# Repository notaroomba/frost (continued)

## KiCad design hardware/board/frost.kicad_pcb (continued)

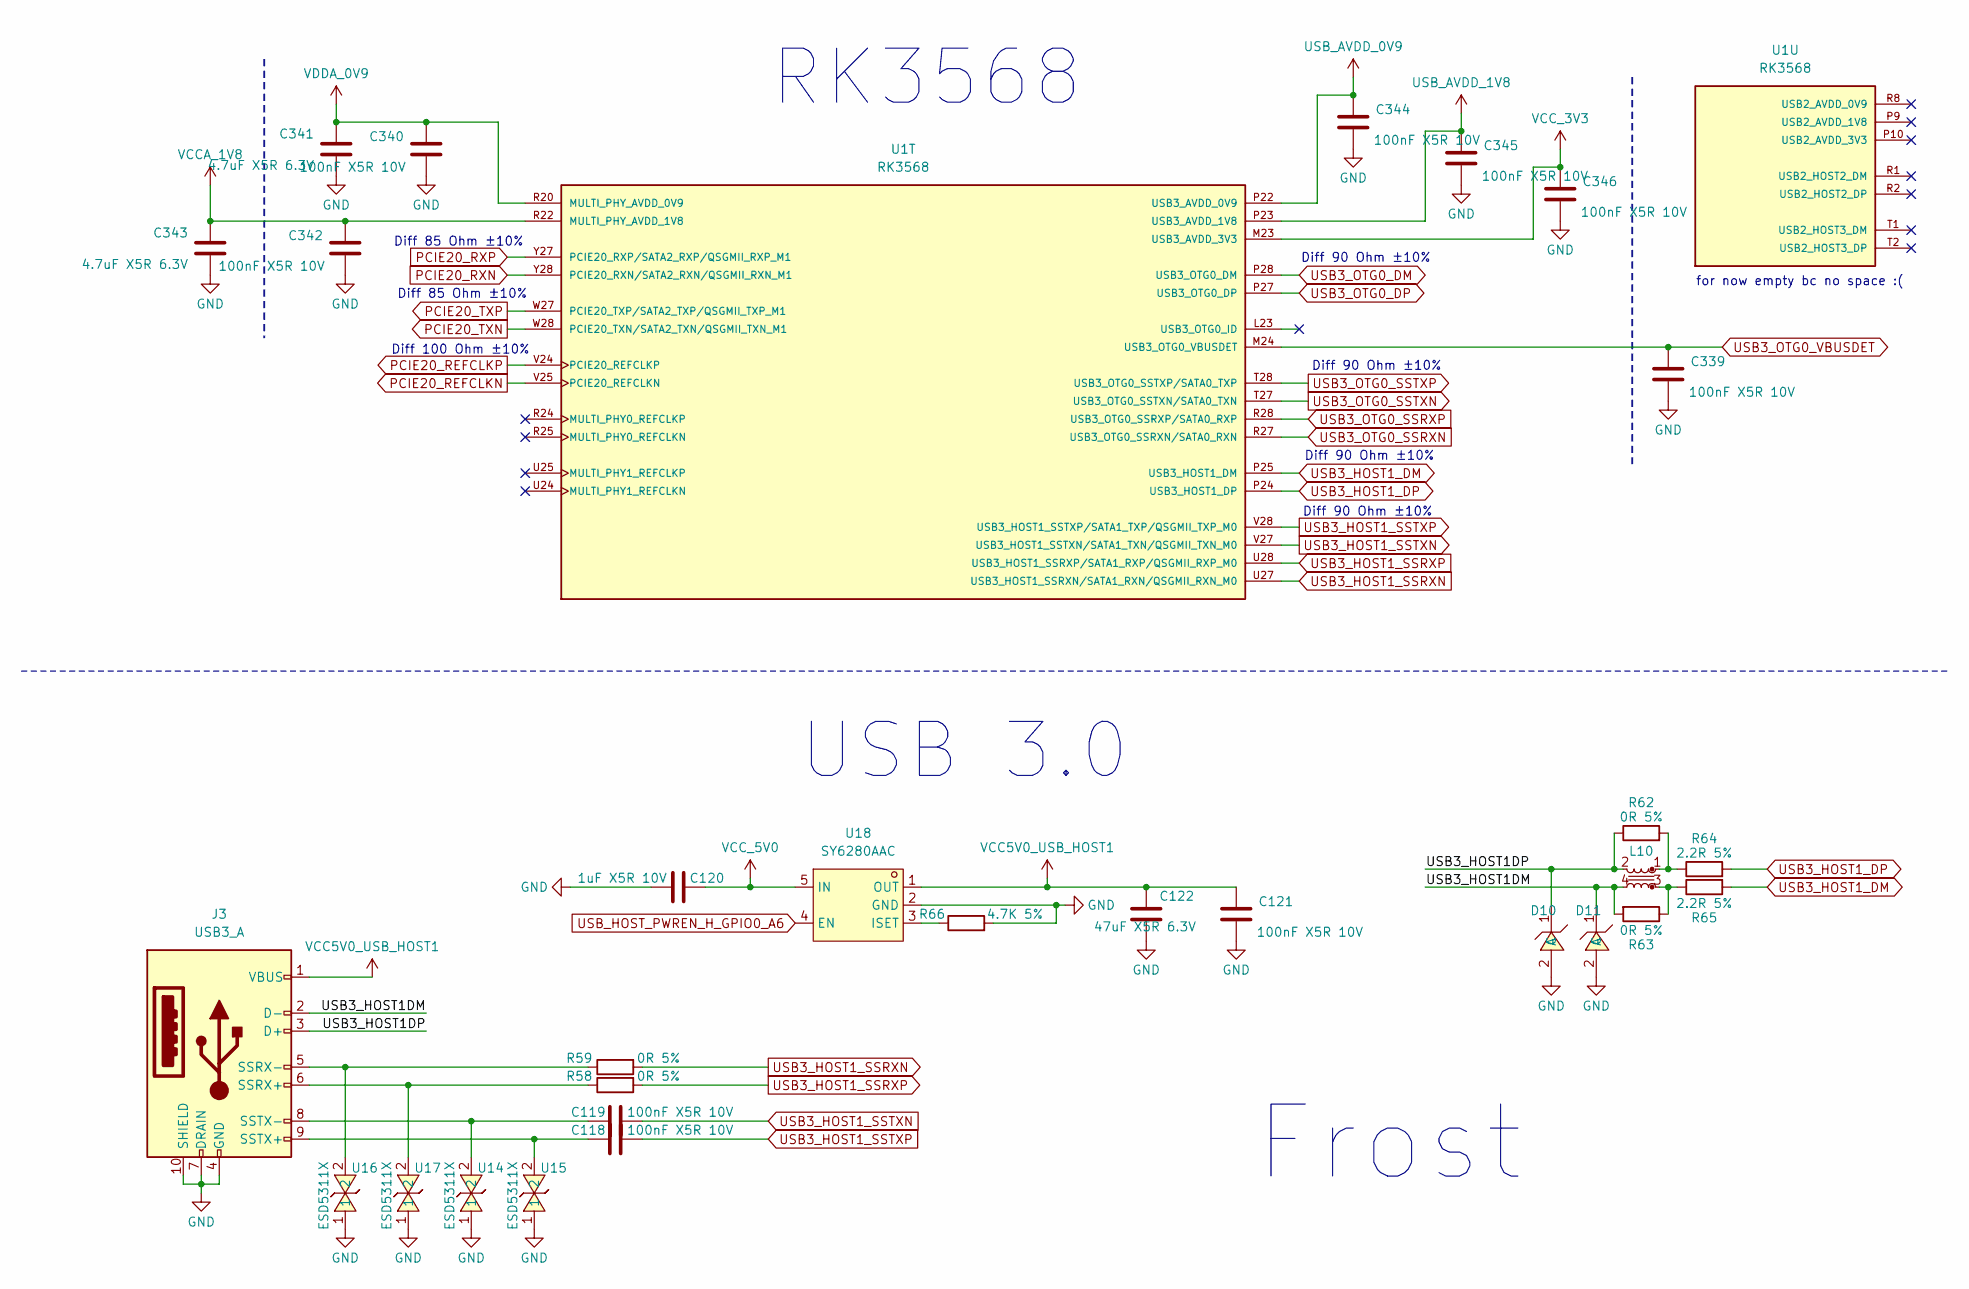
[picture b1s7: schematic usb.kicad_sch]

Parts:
C118, C119, C340, C342, C344, C345, C346: 100nF X5R 10V; C_0201_0603Metric
C120: 1uF X5R 10V; C_0402_1005Metric
C121, C339: 100nF X5R 10V; C_0402_1005Metric
C122: 47uF X5R 6.3V; C_0805_2012Metric
C341, C343: 4.7uF X5R 6.3V; C_0402_1005Metric
D10, D11: BZT52C5V1_C173407; SOD-123_L2.7-W1.6-LS3.7-RD; LCSC Part C173407
J3: USB3_A; USB-A-SMD_U-A-39SS-W-1
L10: L_Iron_Coupled_Small; FILTER-SMD_4P-L2.0-W1.2-BL_DLW21H
R58, R59: 0R 5%; R_0201_0603Metric
R62, R63: 0R 5%; R_0402_1005Metric
R64, R65: 2.2R 5%; R_0402_1005Metric
R66: 4.7K 5%; R_0402_1005Metric
U1: RK3568; BGA636C65P28X28_1900X1900X168; PARTREV 1.3; LCSC C3345225
U14, U15, U16, U17: ESD5311X; DFN1006-2L-BI; LCSC Part C2844730
U18: SY6280AAC; SOT-23-5_L3.0-W1.7-P0.95-LS2.8-BL; LCSC Part C55136

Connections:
/USB/USB3_HOST1DM: D11.1 (C), J3.2 (D-), L10.4, R63.2
/USB/USB3_HOST1DP: D10.1 (C), J3.3 (D+), L10.2, R62.1
unnamed: J3.6 (SSRX+), R58.1, U17.2
unnamed: J3.5 (SSRX-), R59.1, U16.2
unnamed: C118.1, J3.9 (SSTX+), U15.2
unnamed: C119.1, J3.8 (SSTX-), U14.2
unnamed: L10.1, R62.2, R64.1
unnamed: L10.3, R63.1, R65.1
unnamed: R66.1, U18.3 (ISET)
PCIE20_REFCLKN: U1.V25 (PCIE20_REFCLKN); also elsewhere on the board
PCIE20_REFCLKP: U1.V24 (PCIE20_REFCLKP); also elsewhere on the board
PCIE20_RXN: U1.Y28 (PCIE20_RXN/SATA2_RXN/QSGMII_RXN_M1); also elsewhere on the board
PCIE20_RXP: U1.Y27 (PCIE20_RXP/SATA2_RXP/QSGMII_RXP_M1); also elsewhere on the board
PCIE20_TXN: U1.W28 (PCIE20_TXN/SATA2_TXN/QSGMII_TXN_M1); also elsewhere on the board
PCIE20_TXP: U1.W27 (PCIE20_TXP/SATA2_TXP/QSGMII_TXP_M1); also elsewhere on the board
USB3_HOST1_DM: R65.2, U1.P25 (USB3_HOST1_DM)
USB3_HOST1_DP: R64.2, U1.P24 (USB3_HOST1_DP)
USB3_HOST1_SSRXN: R59.2, U1.U27 (USB3_HOST1_SSRXN/SATA1_RXN/QSGMII_RXN_M0)
USB3_HOST1_SSRXP: R58.2, U1.U28 (USB3_HOST1_SSRXP/SATA1_RXP/QSGMII_RXP_M0)
USB3_HOST1_SSTXN: C119.2, U1.V27 (USB3_HOST1_SSTXN/SATA1_TXN/QSGMII_TXN_M0)
USB3_HOST1_SSTXP: C118.2, U1.V28 (USB3_HOST1_SSTXP/SATA1_TXP/QSGMII_TXP_M0)
USB3_OTG0_DM: U1.P28 (USB3_OTG0_DM); also elsewhere on the board
USB3_OTG0_DP: U1.P27 (USB3_OTG0_DP); also elsewhere on the board
USB3_OTG0_SSRXN: U1.R27 (USB3_OTG0_SSRXN/SATA0_RXN); also elsewhere on the board
USB3_OTG0_SSRXP: U1.R28 (USB3_OTG0_SSRXP/SATA0_RXP); also elsewhere on the board
USB3_OTG0_SSTXN: U1.T27 (USB3_OTG0_SSTXN/SATA0_TXN); also elsewhere on the board
USB3_OTG0_SSTXP: U1.T28 (USB3_OTG0_SSTXP/SATA0_TXP); also elsewhere on the board
USB3_OTG0_VBUSDET: C339.1, U1.M24 (USB3_OTG0_VBUSDET); also elsewhere on the board
USB_AVDD_0V9: C344.1, U1.P22 (USB3_AVDD_0V9); also elsewhere on the board
USB_AVDD_1V8: C345.1, U1.P23 (USB3_AVDD_1V8); also elsewhere on the board
USB_HOST_PWREN_H_GPIO0_A6: U18.4 (EN); also elsewhere on the board
VCC5V0_USB_HOST1: C121.1, C122.2, J3.1 (VBUS), U18.1 (OUT)
VCCA_1V8: C342.1, C343.1, U1.R22 (MULTI_PHY_AVDD_1V8); also elsewhere on the board
VCC_3V3: C346.1, U1.M23 (USB3_AVDD_3V3); also elsewhere on the board
VCC_5V0: C120.2, U18.5 (IN); also elsewhere on the board
VDDA_0V9: C340.1, C341.1, U1.R20 (MULTI_PHY_AVDD_0V9), U1.R21 (MULTI_PHY_AVDD_0V9); also elsewhere on the board

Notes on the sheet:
Frost
Diff 85 Ohm ±10%
for now empty bc no space :(
Diff 90 Ohm ±10%
USB 3.0
Diff 100 Ohm ±10%
RK3568

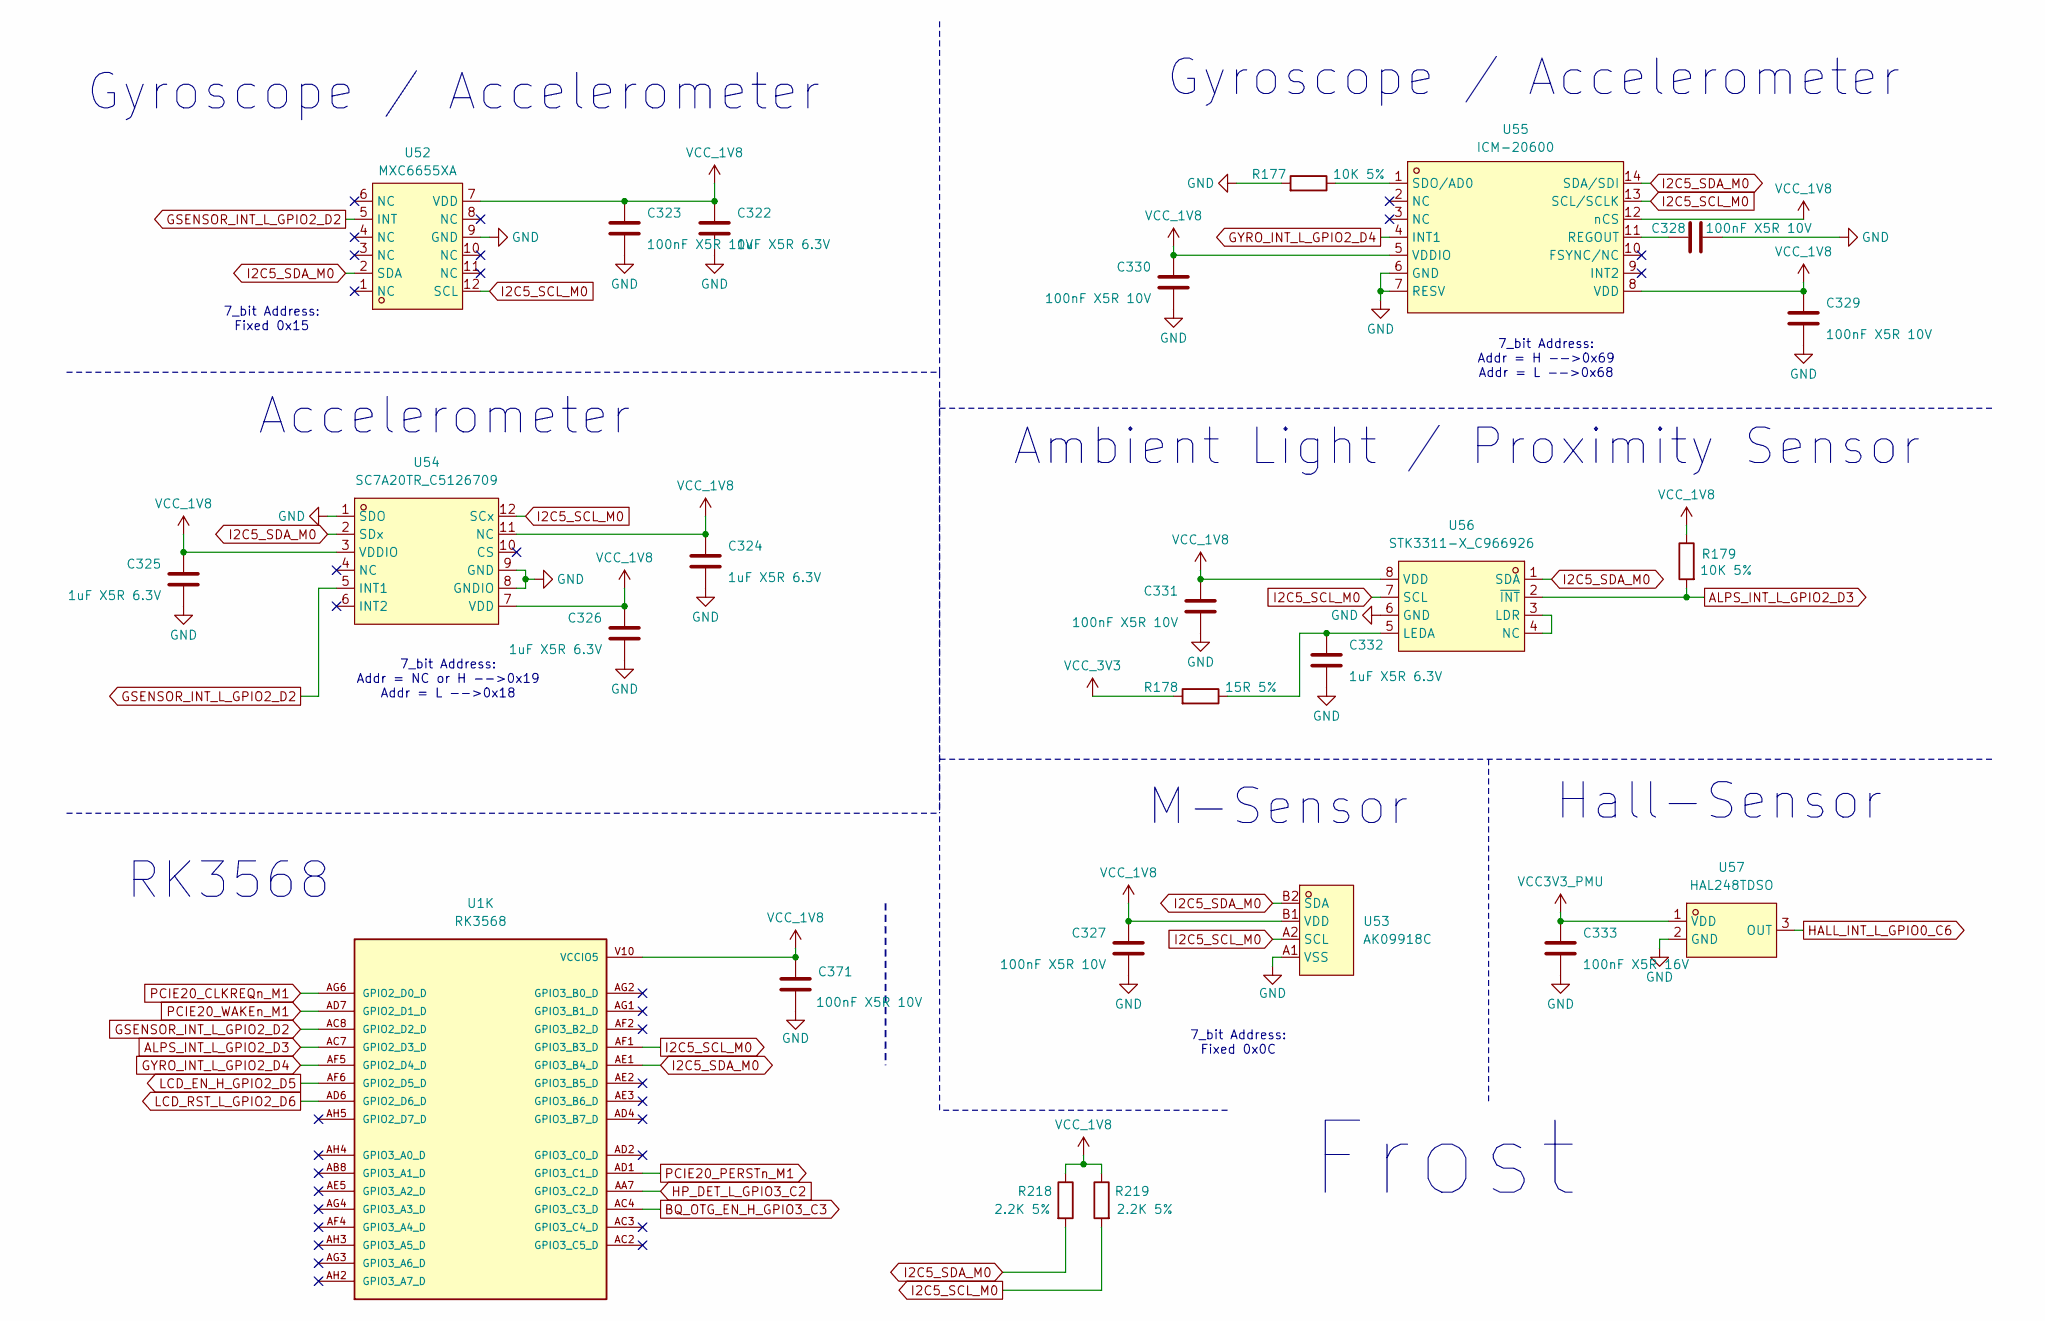
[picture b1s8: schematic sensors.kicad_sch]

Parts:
C322, C324, C325, C326, C332: 1uF X5R 6.3V; C_0402_1005Metric
C323, C327, C328, C329, C330, C331: 100nF X5R 10V; C_0402_1005Metric
C333: 100nF X5R 16V; C_0402_1005Metric
C371: 100nF X5R 10V; C_0201_0603Metric
R177, R179: 10K 5%; R_0402_1005Metric
R178: 15R 5%; R_0402_1005Metric
R218, R219: 2.2K 5%; R_0402_1005Metric
U1: RK3568; BGA636C65P28X28_1900X1900X168; PARTREV 1.3; LCSC C3345225
U52: MXC6655XA; LGA-12_L2.0-W2.0-P0.50-TL_BOSCH_BMA490L; LCSC Part C5189050
U53: AK09918C; WLCSP-4_L0.8-W0.8-R2-C2-P0.40-BL-1; LCSC Part C2655004
U54: SC7A20TR_C5126709; LGA-12_L2.0-W2.0-P0.50-BL; LCSC Part C5126709
U55: ICM-20600; LGA-14_L3.0-W2.5-P0.50-BL; LCSC Part C124140
U56: STK3311-X_C966926; LGA-8_L4.0-W2.4-P0.97-BR; LCSC Part C966926
U57: HAL248TDSO; SOT-23-3_L2.9-W1.6-P1.90-LS2.8-BR-CW; LCSC Part C19089538

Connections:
ALPS_INT_L_GPIO2_D3: R179.2, U1.AC7 (GPIO2_D3_D), U56.2 (~INT)
BQ_OTG_EN_H_GPIO3_C3: U1.AC4 (GPIO3_C3_D); also elsewhere on the board
GSENSOR_INT_L_GPIO2_D2: U1.AC8 (GPIO2_D2_D), U52.5 (INT), U54.5 (INT1)
GYRO_INT_L_GPIO2_D4: U1.AF5 (GPIO2_D4_D), U55.4 (INT1)
HALL_INT_L_GPIO0_C6: U57.3 (OUT); also elsewhere on the board
HP_DET_L_GPIO3_C2: U1.AA7 (GPIO3_C2_D); also elsewhere on the board
I2C5_SCL_M0: R219.2, U1.AF1 (GPIO3_B3_D), U52.12 (SCL), U53.A2 (SCL), U54.12 (SCx), U55.13 (SCL/SCLK), U56.7 (SCL)
I2C5_SDA_M0: R218.2, U1.AE1 (GPIO3_B4_D), U52.2 (SDA), U53.B2 (SDA), U54.2 (SDx), U55.14 (SDA/SDI), U56.1 (SDA)
LCD_EN_H_GPIO2_D5: U1.AF6 (GPIO2_D5_D)
LCD_RST_L_GPIO2_D6: U1.AD6 (GPIO2_D6_D); also elsewhere on the board
unnamed: C328.1, U55.11 (REGOUT)
unnamed: R177.1, U55.1 (SDO/AD0)
unnamed: U56.3 (LDR), U56.4 (NC)
unnamed: C332.1, R178.1, U56.5 (LEDA)
PCIE20_CLKREQn_M1: U1.AG6 (GPIO2_D0_D); also elsewhere on the board
PCIE20_PERSTn_M1: U1.AD1 (GPIO3_C1_D); also elsewhere on the board
PCIE20_WAKEn_M1: U1.AD7 (GPIO2_D1_D); also elsewhere on the board
VCC3V3_PMU: C333.1, U57.1 (VDD); also elsewhere on the board
VCC_1V8: C322.1, C323.1, C324.1, C325.1, C326.1, C327.1, C329.1, C330.1, C331.1, C371.1, R179.1, R218.1, R219.1, U1.V10 (VCCIO5), U1.V11 (VCCIO5), U52.7 (VDD), U53.B1 (VDD), U54.3 (VDDIO), U54.7 (VDD), U54.11 (NC), U55.5 (VDDIO), U55.8 (VDD), U55.12 (nCS), U56.8 (VDD); also elsewhere on the board
VCC_3V3: R178.2; also elsewhere on the board

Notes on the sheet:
RK3568
Frost
Gyroscope / Accelerometer
Ambient Light / Proximity Sensor
7_bit Address: Fixed 0x15
M-Sensor
Hall-Sensor
7_bit Address: Fixed 0x0C
7_bit Address: Addr = H -->0x69 Addr = L -->0x68
Accelerometer
7_bit Address: Addr = NC or H -->0x19 Addr = L -->0x18

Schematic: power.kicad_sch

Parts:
C3, C4, C5, C6, C21, C23: 10uF X5R 25V; C_0805_2012Metric
C7, C19, C30, C41, C43, C65, C69, C71, C76, C89, C112, C114, C334, C336: 10uF X5R 10V; C_0603_1608Metric
C8, C9, C10, C15, C20, C31, C32, C35, C40, C42, C53, C54, C61, C64, C68, C80, C97, C98, C113, C199, C335: 100nF X5R 10V; C_0402_1005Metric
C11, C12, C13, C14, C262, C265, C270, C372: 100nF X5R 10V; C_0201_0603Metric
C16, C17: 220pF C0G 25V; C_0402_1005Metric
C18, C50, C57, C74, C83, C84, C85: 1uF X5R 10V; C_0402_1005Metric
C22: 100pF C0G 50V; C_0402_1005Metric
C24: 4.7uF X5R 10V; C_0402_1005Metric
C25: 47nF X5R 25V; C_0402_1005Metric
C26, C27, C28, C29, C37: 10uF X5R 10V; C_0805_2012Metric
C33, C38: 22pF C0G 50V; C_0402_1005Metric
C34, C58, C59, C60, C62, C63, C66, C67, C70, C77, C78, C104, C105, C106, C255, C256, C257, C259, C260, C263, C269, C271, C272: 22uF X5R 6.3V; C_0603_1608Metric
C36, C55, C56: 100nF X5R 16V; C_0402_1005Metric
C39, C102, C103: 22uF X5R 10V; C_0805_2012Metric
C44, C86, C254, C261, C264: 4.7uF X5R 6.3V; C_0402_1005Metric
C45, C46, C47, C48, C49, C72, C73, C75, C79, C81, C82, C87, C88, C91, C93, C94, C101, C107, C108, C109, C110, C111, C115, C116, C266, C267: 1uF X5R 6.3V; C_0402_1005Metric
C51, C52: 20pF C0G 50V; C_0402_1005Metric
C90: 4.7uF X5R 10V; C_0603_1608Metric
C92: 2.2uF X5R 10V; C_0402_1005Metric
C95, C96: 27pF C0G 50V; C_0402_1005Metric
C99, C100: 680pF C0G 50V; C_0402_1005Metric
C117: 4.7uF X5R 6.3V; C_0603_1608Metric
C258, C268, C273: 10uF X5R 6.3V; C_0603_1608Metric
D1: BZT52C5V1_C173407; SOD-123_L2.7-W1.6-LS3.7-RD; LCSC Part C173407
D6, D7: ESD5344D; DFN2510-10_L2.5-W1.0-P0.50-BL; LCSC Part C6562203
D8: LED; LED_0603_1608Metric
D9: SS32; D_SMA
FB1, FB2, FB3, FB4, FB7, FB8, FB9, FB10: 120@100MHz 0.03R; L_0603_1608Metric; LCSC C85831
FB5, FB6: 180@100M 1.5A; L_0603_1608Metric; LCSC C268312
L1: L_Iron_Coupled_Small; FILTER-SMD_4P-L2.0-W1.2-BL_DLW21H
L2: SLO0520H1R0MTT; IND-SMD_L5.4-W5.1; LCSC Part C325980
L3, L4: LVF404026-2R2M-N; IND-SMD_L4.0-W4.0; LCSC Part C2847115
Q1: WPM3407-3/TR; SOT-23-3_L3.0-W1.7-P0.95-LS2.9-BR; LCSC Part C167139
Q2, Q5: SS8050; SOT-23
Q3, Q4, Q9: WPM2015-3/TR_C7472861; SOT-23-3_L2.9-W1.3-P1.90-LS2.4-BR; LCSC Part C7472861
R3: 0R; R_1206_3216Metric
R4: 470R 5%; R_0805_2012Metric
R5, R17, R20, R24, R26, R29, R34, R51, R53, R57, R190: 10K 5%; R_0402_1005Metric
R6: 15K 5%; R_0402_1005Metric
R7, R8: 2.2R 5%; R_0402_1005Metric
R9, R12, R19, R31, R32, R33, R45, R54, R55, R56: 0R 5%; R_0402_1005Metric
R10, R11: 0R 5%; R_0201_0603Metric
R13: 330R 5%; R_0402_1005Metric
R14, R40, R41, R42, R49: 100R 5%; R_0402_1005Metric
R15: 5.1K 1%; R_0402_1005Metric
R16, R37, R39: 30K 1%; R_0402_1005Metric
R18: 0.01R 1%; R_1206_3216Metric
R21: 232K 1%; R_0402_1005Metric
R22: 49.9K 1%; R_0402_1005Metric
R23, R30, R47, R50, R192: 100K 5%; R_0402_1005Metric
R25, R48, R52: 51K 5%; R_0402_1005Metric
R27: 360K 1%; R_0402_1005Metric
R28, R43: 47K 1%; R_0402_1005Metric
R35, R36, R220, R221, R223, R224: 22R 5%; R_0402_1005Metric
R38: 20K 1%; R_0402_1005Metric
R44: 120K 1%; R_0402_1005Metric
R46: 30K 5%; R_0402_1005Metric
R191: 100K 5%; R_0402_1005Metric; not fitted
U1: RK3568; BGA636C65P28X28_1900X1900X168; PARTREV 1.3; LCSC C3345225
U4: RK809-5; QFN-68_L7.0-W7.0-P0.35-BL-EP5.5; LCSC Part C2939628
U6: TMUXHS4212RKSR; TQFN-20_L4.5-W2.5-P0.50-BL-EP3.0; LCSC Part C2869871
U7: FUSB302BMPX; WQFN-14-1EP_2.5x2.5mm_P0.5mm_EP1.45x1.45mm
U8: BQ25890RTWR; WQFN-24_L4.0-W4.0-P0.50-BL-EP; LCSC Part C130451
U9: S2B-PH-K-S(LF)(SN); CONN-TH_S2B-PH-K-S-LF-SN; LCSC Part C173752
U10, U64, U65, U66, U67: FTC252012SR47MBCA; IND-SMD_L2.5-W2.0; LCSC Part C5832368
U11: RK860-0; WLCSP-20_L2.0-W1.6-R5-C4-P0.40-TL; LCSC Part C19188628
U12: SY7208ABC; SOT-23-6_L2.9-W1.6-P0.95-LS2.8-BR; LCSC Part C80514
U13: FTC252012SR24MBCA; IND-SMD_L2.5-W2.0_MHCHL2520; LCSC Part C5832366
U63: SY8089AAAC; SOT-23-5_L3.0-W1.7-P0.95-LS2.8-BR; LCSC Part C78988
U68, U69, U70, U71: ESD5341N; DFN1006-2L-RD; LCSC Part C3021106
USBC1: 105450-0101; USB-C-SMD_TYPE-C-USB-18; LCSC Part C134092
X2: Q13FC1350000400; FC-135R_L3.2-W1.5; LCSC Part C32346

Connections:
/Power/PMIC_XIN: C51.1, U4.50 (XIN), X2.2
/Power/PMIC_XOUT: C52.1, U4.51 (XOUT), X2.1
/Power/SNSN: C55.1, R19.2, U4.63 (SNSN)
/Power/SNSP: C55.2, R18.1, U4.62 (SNSP), U9.1
/Power/TYPEC_0_CC1: C16.1, U7.10 (CC1), U7.11 (CC1), U69.1, USBC1.A5 (CC1)
/Power/TYPEC_0_CC2: C17.1, U7.1 (CC2), U7.14 (CC2), U68.1, USBC1.B5 (CC2)
/Power/TYPEC_0_DM: L1.3, L1.4, R8.1, U71.1, USBC1.A7 (D-), USBC1.B6 (D+)
/Power/TYPEC_0_DP: L1.1, L1.2, R7.1, U70.1, USBC1.A6 (D+), USBC1.B7 (D-)
/Power/TYPEC_0_SSRX1N: D6.5, D6.6, U6.16 (B1n), USBC1.B10 (RX1-)
/Power/TYPEC_0_SSRX1P: D6.4, D6.7, U6.17 (B1p), USBC1.B11 (RX1+)
/Power/TYPEC_0_SSRX2N: D7.4, D7.7, U6.12 (C1n), USBC1.A10 (RX2-)
/Power/TYPEC_0_SSRX2P: D7.5, D7.6, U6.13 (C1p), USBC1.A11 (RX2+)
/Power/TYPEC_0_SSTX1N: C13.1, D6.2, D6.9, USBC1.A3 (TX1-)
/Power/TYPEC_0_SSTX1P: C14.1, D6.1, D6.10, USBC1.A2 (TX1+)
/Power/TYPEC_0_SSTX2N: C11.1, D7.1, D7.10, USBC1.B3 (TX2-)
/Power/TYPEC_0_SSTX2P: C12.1, D7.2, D7.9, USBC1.B2 (TX2+)
BQ_OTG_EN_H_GPIO3_C3: U8.8 (OTG); also elsewhere on the board
CHG_INT_L_GPIO0_C2: U8.7 (INT); also elsewhere on the board
CHG_REF: C24.1, D8.2 (A), R15.1, U8.22 (REGN)
FLASH_VOL_SEL: R57.1; also elsewhere on the board
HPL_OUT: U4.39 (HPL_OUT); also elsewhere on the board
HPR_OUT: U4.41 (HPR_OUT); also elsewhere on the board
HP_SNS: U4.40 (HP_SNS); also elsewhere on the board
I2C0_SCL_PMIC: R35.2, U7.6 (SCL), U8.5 (SCL), U11.A3 (SCL); also elsewhere on the board
I2C0_SDA_PMIC: R36.2, U7.7 (SDA), U8.6 (SDA), U11.B1 (SDA); also elsewhere on the board
I2S1_LRCK_TX_M0_PMIC: R223.2, U4.14 (LRCLK)
I2S1_MCLK_M0_PMIC: R220.2, U4.16 (MCLK)
I2S1_SCLK_TX_M0_PMIC: R221.2, U4.15 (BCLK)
I2S1_SDI0_M0/PDM_SDI0_M0_PMIC: U1.B21 (GPIO1_B3_D), U4.18 (SDO/PDMDATA)
I2S1_SDO0_M0_PMIC: U1.B20 (GPIO1_A7_D), U4.17 (SDI)
LCD0_PWREN_H_GPIO0_C7: R53.2; also elsewhere on the board
MIC1_INN: C97.1; also elsewhere on the board
MIC1_INP: C98.1
MIPI_AVDD_0V9: FB9.2; also elsewhere on the board
MIPI_AVDD_1V8: FB10.2; also elsewhere on the board
unnamed: C25.1, L2.2, U8.19 (SW), U8.20 (SW)
unnamed: D8.1 (K), R13.2
unnamed: D9.2 (A), L3.2, U12.1 (LX)
unnamed: C37.1, L3.1, Q1.3 (D), U12.4 (EN), U12.5 (IN)
unnamed: Q1.1 (G), R24.2
unnamed: Q2.1 (B), R25.2, R26.2
unnamed: Q2.3 (C), R24.1
unnamed: C42.2, Q3.1 (G), R29.2
unnamed: C113.2, Q4.1 (G), R50.1, R51.2
unnamed: Q5.1 (B), R52.2, R53.1
unnamed: Q5.3 (C), R51.1
unnamed: C335.2, Q9.1 (G), R190.2, R192.1
unnamed: R37.1, R39.2
unnamed: R220.1, U1.A19 (GPIO1_A2_D)
unnamed: R221.1, U1.B19 (GPIO1_A3_D)
unnamed: R223.1, U1.A20 (GPIO1_A5_D)
unnamed: R224.1, U1.C20 (GPIO1_A6_D)
unnamed: R37.2, R38.2, U4.56 (BATDIV)
unnamed: R33.2, U4.68 (CLK32K)
unnamed: C90.2, U4.36 (CPN)
unnamed: C90.1, U4.37 (CPP)
unnamed: R43.1, R44.2, U4.27 (FB3)
unnamed: R45.1, U4.59 (FB5)
unnamed: C96.1, C97.2, U4.42 (MICIN)
unnamed: C95.1, C98.2, U4.43 (MICIP)
unnamed: R35.1, U4.1 (SCL)
unnamed: R36.1, U4.2 (SDA)
unnamed: FB6.2, U4.34 (SPKN_OUT)
unnamed: FB5.2, U4.32 (SPKP_OUT)
unnamed: U4.12 (SW1), U64.2
unnamed: U4.9 (SW2), U10.2
unnamed: U4.25 (SW3), U65.2
unnamed: U4.65 (SW4), U67.1
unnamed: U4.53 (SW5), U66.1
unnamed: C94.1, U4.44 (VCC_1P8A)
unnamed: C93.1, U4.48 (VCC_1P8D)
unnamed: C91.1, U4.38 (VCC_CPVDD)
unnamed: C92.1, U4.35 (VCC_CPVSS)
unnamed: C89.1, FB4.2, U4.33 (VCC_SPK_HP)
unnamed: C80.2, R46.1, R47.1, U4.61 (VDC)
unnamed: C50.1, U4.46 (VREF)
unnamed: R10.2, U6.8 (A1n)
unnamed: R11.2, U6.7 (A1p)
unnamed: C13.2, U6.18 (B0n)
unnamed: C14.2, U6.19 (B0p)
unnamed: C11.2, U6.14 (C0n)
unnamed: C12.2, U6.15 (C0p)
unnamed: R9.2, U6.2 (OEn)
unnamed: C25.2, U8.21 (BTST)
unnamed: R14.1, U8.10 (ILIM)
unnamed: C23.2, U8.23 (PMID)
unnamed: R13.1, U8.4 (STAT)
unnamed: C22.1, R15.2, R16.1, R17.1, U8.11 (TS)
unnamed: R12.1, U8.9 (~CE)
unnamed: R48.1, U11.A2 (EN)
unnamed: U11.D3 (LX), U11.D4 (LX), U11.E3 (LX), U11.E4 (LX), U13.1
unnamed: C38.2, R27.1, R28.2, U12.3 (FB)
unnamed: C32.1, R20.1, U63.1 (EN)
unnamed: C33.2, R21.1, R22.2, U63.5 (FB)
unnamed: L4.1, U63.3 (LX)
PDM_CLK0_M0_PMIC: R224.2, U4.19 (PDMCLK)
PMIC_32KOUT_WIFI: R33.1; also elsewhere on the board
PMIC_INT_L: U4.7 (INT); also elsewhere on the board
PMIC_PWRON: C54.1, U4.52 (PWRON); also elsewhere on the board
PMIC_SLEEP_H: R29.1, R30.2, U4.49 (SLEEP), U11.A1 (VSEL); also elsewhere on the board
PMUIO2: C115.1, R54.1, R55.2; also elsewhere on the board
RESETn: C53.1, R34.2, U4.67 (RESETB); also elsewhere on the board
SDMMC0_PWREN_L: R190.1, R191.2; also elsewhere on the board
SPKN_OUT: C100.2, FB6.1
SPKP_OUT: C99.2, FB5.1
TYPEC_SW_SEL_GPIO4_D2: U6.9 (SEL); also elsewhere on the board
USB3_OTG0_DM: R8.2; also elsewhere on the board
USB3_OTG0_DP: R7.2; also elsewhere on the board
USB3_OTG0_SSRXN: R10.1; also elsewhere on the board
USB3_OTG0_SSRXP: R11.1; also elsewhere on the board
USB3_OTG0_SSTXN: U6.4 (A0n); also elsewhere on the board
USB3_OTG0_SSTXP: U6.3 (A0p); also elsewhere on the board
USB3_OTG0_VBUSDET: R5.2, R6.2; also elsewhere on the board
USB5V0_EN_H_GPIO0_D6: R26.1; also elsewhere on the board
USBCC_INT_L_GPIO0_C5: U7.5 (INT_N); also elsewhere on the board
USB_AVDD_0V9: FB7.2; also elsewhere on the board
USB_AVDD_1V8: FB8.2; also elsewhere on the board
VBUS_DC5V: D1.1 (C), R4.2, R5.1, R47.2
VBUS_TYPEC: C5.1, C6.1, C15.1, R3.2, R4.1, U7.2 (VBUS)
VBUS_TYPEC_0: C3.1, C4.1, C21.1, R3.1, U8.1 (VBUS), USBC1.A4 (VBUS), USBC1.A9 (VBUS), USBC1.B4 (VBUS), USBC1.B9 (VBUS)
VCC3V3_LCD0: C114.1, Q4.3 (D); also elsewhere on the board
VCC3V3_PMU: C18.1, C88.1, R20.2, R34.1, R48.2, R57.2, U4.31 (LDO6), U7.3 (VDD), U7.4 (VDD); also elsewhere on the board
VCC3V3_SD: C79.2, C336.1, Q9.3 (D), U4.58 (SWOUT2); also elsewhere on the board
VCC3V3_SYS: C19.1, C20.1, C33.1, C34.1, C35.1, C41.1, C42.1, C75.2, C112.1, C113.1, C334.1, C335.1, L4.2, Q3.2 (S), Q4.2 (S), Q9.2 (S), R21.2, R50.2, R192.2, U4.57 (VCC8), U7.12 (VCONN), U7.13 (VCONN); also elsewhere on the board
VCC3V3_U3_SW: C7.1, C8.1, C9.1, C10.1, FB1.2, U6.1 (RSVD1), U6.6 (VCC), U6.10 (RSVD2)
VCCA1V8_IMAGE: C48.1, C111.1, FB3.2, FB10.1; also elsewhere on the board
VCCA1V8_IMAGE_P: C81.2, U4.6 (LDO9); also elsewhere on the board
VCCA1V8_PMU: C82.2, R54.2, U4.5 (LDO8); also elsewhere on the board
VCCA_1V8: C49.1, C109.1, FB8.1, R32.1; also elsewhere on the board
VCCA_1V8_P: C101.2, R32.2, U4.3 (LDO7)
VCCIO_ACODEC: C86.2, C372.1, U1.H17 (VCCIO1), U4.28 (LDO4); also elsewhere on the board
VCCIO_FLASH: C117.1, R56.1; also elsewhere on the board
VCCIO_SD: C87.1, U4.29 (LDO5); also elsewhere on the board
VCCIO_WL: C116.1, R55.1; also elsewhere on the board
VCC_1V8: C47.1, C77.1, C78.1, FB3.1, R45.2, R56.2, U66.2; also elsewhere on the board
VCC_3V3: C43.1, FB1.1, Q3.3 (D); also elsewhere on the board
VCC_5V0: C38.1, C39.1, C40.1, D9.1 (K), FB4.1, R27.2; also elsewhere on the board
VCC_BAT: C28.1, C29.1, C56.1, R39.1, U8.13 (BAT), U8.14 (BAT), U9.2
VCC_DDR: C70.1, C71.1, R43.2, U4.26 (VBUCK3), U65.1; also elsewhere on the board
VCC_SYSIN: C26.1, C27.1, C30.1, C31.1, C36.1, C57.1, C58.1, C65.1, C69.1, C72.2, C73.2, C74.2, C76.1, C102.1, C103.1, L2.1, Q1.2 (S), R23.2, U4.4 (VCC7), U4.10 (VCC2), U4.11 (VCC1), U4.22 (VCC5), U4.24 (VCC3), U4.30 (VCC6), U4.45 (VCC_RTC), U4.54 (VCC9), U4.66 (VCC4), U8.15 (SYS), U8.16 (SYS), U11.D1 (VIN), U11.D2 (VIN), U11.E1 (VIN), U11.E2 (VIN), U63.4 (IN); also elsewhere on the board
VDDA0V9_IMAGE: C45.1, C110.1, FB2.2, FB9.1; also elsewhere on the board
VDDA0V9_IMAGE_P: C83.2, U4.23 (LDO1); also elsewhere on the board
VDDA0V9_PMU: C85.2, U4.20 (LDO3); also elsewhere on the board
VDDA_0V9: C46.1, C108.1, FB7.1, R31.1; also elsewhere on the board
VDDA_0V9_P: C84.2, R31.2, U4.21 (LDO2)
VDD_CPU: C104.1, C105.1, C106.1, C107.2, C199.1, C254.1, C255.1, C256.1, C257.1, R49.1, U1.J15 (VDD_CPU), U1.K15 (VDD_CPU), U1.K16 (VDD_CPU), U1.K17 (VDD_CPU), U1.K18 (VDD_CPU), U1.L15 (VDD_CPU), U1.L16 (VDD_CPU), U1.L17 (VDD_CPU), U1.L18 (VDD_CPU), U1.M17 (VDD_CPU), U13.2
VDD_CPU_COM: C107.1, R49.2, U1.M15 (VDD_CPU_COM), U11.A4 (VOUT)
VDD_GPU: C62.1, C63.1, C64.1, C64.2, C258.1, C259.1, C260.1, C261.1, C262.1, R41.1, R41.2, U1.R13 (VDD_GPU), U1.T13 (VDD_GPU), U1.U11 (VDD_GPU), U1.U12 (VDD_GPU), U1.U13 (VDD_GPU), U4.8 (FB2), U10.1
VDD_LOGIC: C44.1, C59.1, C60.1, C61.1, C61.2, C263.1, C264.1, C265.1, C266.1, C267.1, C268.1, C269.1, FB2.1, R40.1, R40.2, U1.L12 (VDD_LOGIC), U1.M12 (VDD_LOGIC), U1.N13 (VDD_LOGIC), U1.N16 (VDD_LOGIC), U1.P13 (VDD_LOGIC), U1.P16 (VDD_LOGIC), U1.R12 (VDD_LOGIC), U1.R16 (VDD_LOGIC), U1.T12 (VDD_LOGIC), U1.T16 (VDD_LOGIC), U4.13 (FB1), U64.1
VDD_NPU: C66.1, C67.1, C68.1, C68.2, C270.1, C271.1, C272.1, C273.1, R42.1, R42.2, U1.M19 (VDD_NPU), U1.N19 (VDD_NPU), U1.P18 (VDD_NPU), U1.P19 (VDD_NPU), U1.P20 (VDD_NPU), U4.64 (FB4), U67.2

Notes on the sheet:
LCD Power
Should be placed under
VCC_3V3_SD
USB/MIPI PHY Power
USB-C / ESD
VDD_CPU
I2C if needed
USB-C PD
Power Schematics
VCC/VDDA
Differential Channel Crossbar Switch
VCC_3V3 (OFF under SLEEP)
Should be placed close
Peripheral power input source
Check feedback resistor depending on RAM type 47k is for LPDDR4
Power
Frost
FLASH
WIFI/BT IO and CTL IO Power
VCC_5V0
Close to BAT SNSP/N are differential
Note: FLASH_VOL_SEL is pulled up if 1.8v and down if 3.3v
VCC3V3_SYS
PMIC RK809
RK3568
Charger IC

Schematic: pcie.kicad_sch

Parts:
C297, C298, C299, C300: 220nF X5R 10V; C_0201_0603Metric
C301, C303: 22uF X5R 6.3V; C_0603_1608Metric
C302, C304, C308, C310, C313, C316, C317, C321: 100nF X5R 10V; C_0402_1005Metric
C305, C306: 18pF C0G 50V; C_0402_1005Metric
C307, C309, C312: 1uF X5R 10V; C_0402_1005Metric
C311, C314: 4.7F X5R 6.3V; C_0402_1005Metric
C315: 10uF X5R 10V; C_0603_1608Metric
C318: 22pF C0G 50V; C_0402_1005Metric
C319: 10uF X5R 6.3V; C_0603_1608Metric
C320: 22pF C0G 50V; CP_Elec_6.3x5.9; LCSC Part C186713
C347, C350: 4.7uF X5R 6.3V; C_0402_1005Metric
C348, C349: 100nF X5R 10V; C_0201_0603Metric
CN2: 1-2199230-5; PCIE-SMD_75P-P0.50_1-2199230-5; LCSC Part C590854
L11: LVF404026-2R2M-N; IND-SMD_L4.0-W4.0; LCSC Part C2847115
R152, R153, R154, R155: 22R 5%; R_0402_1005Metric
R156: 2.2R 5%; R_0402_1005Metric
R157, R158, R161, R162: 33R 5%; R_0201_0603Metric
R159, R160, R163, R164: 49.9R 1%; R_0201_0603Metric
R165, R173: 470R 1%; R_0402_1005Metric
R166, R167, R169, R171, R172, R174: 10K 5%; R_0402_1005Metric
R168, R170: 10K 5%; R_0402_1005Metric; not fitted
R175: 232K 1%; R_0402_1005Metric
R176: 49.9K 1%; R_0402_1005Metric
R197: 200R 1%; R_0201_0603Metric
TP1, TP2, TP3, TP4: TestPoint; TestPoint_Pad_D1.0mm
U1: RK3568; BGA636C65P28X28_1900X1900X168; PARTREV 1.3; LCSC C3345225
U46: PI6C557-03BLE; TSSOP-16_L5.0-W4.4-P0.65-LS6.4-BL; LCSC Part C150743
U50: TP5108E23E-33; SOT-23-5_L3.0-W1.7-P0.95-LS2.8-BL; LCSC Part C587168
U51: SY8089AAAC; SOT-23-5_L3.0-W1.7-P0.95-LS2.8-BR; LCSC Part C78988
X6: X322525MOB4SI; CRYSTAL-SMD_4P-L3.2-W2.5-BL; LCSC Part C9006

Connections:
/PCIE/PI6C_03_OE: R172.1, U46.6 (OE)
/PCIE/PI6C_03_S0: R166.1, U46.1 (S0)
/PCIE/PI6C_03_S1: R167.1, U46.2 (S1)
/PCIE/PI6C_03_SS0: R168.1, R169.1, U46.3 (SS0)
/PCIE/PI6C_03_SS1: R170.1, R171.1, U46.8 (SS1)
unnamed: C297.1, CN2.49
unnamed: C298.1, CN2.47
unnamed: C299.1, CN2.35
unnamed: C300.1, CN2.37
unnamed: CN2.10, TP4.1
unnamed: CN2.38, TP1.1
unnamed: CN2.50, R153.2
unnamed: CN2.52, R152.2
unnamed: CN2.54, R154.2
unnamed: CN2.56, TP3.1
unnamed: CN2.58, TP2.1
unnamed: R197.2, U1.U19 (PCIE30_RESREF)
unnamed: R158.2, U46.15 (CLK0)
unnamed: R161.2, U46.11 (CLK1)
unnamed: R165.1, U46.9 (IREF)
unnamed: C309.1, C310.1, R156.2, U46.12 (VDDA)
unnamed: C306.1, U46.4 (X1/CLK), X6.3 (OSC2)
unnamed: R155.1, U46.5 (X2)
unnamed: R157.2, U46.14 (~CLK0)
unnamed: R162.2, U46.10 (~CLK1)
unnamed: C313.1, R173.1, U50.3 (CE)
unnamed: C317.1, R174.2, U51.1 (EN)
unnamed: C318.2, R175.2, R176.1, U51.5 (FB)
unnamed: L11.1, U51.3 (LX)
unnamed: C305.1, R155.2, X6.1 (OSC1)
PCIE30X2_CLKREQn_M2: R152.1; also elsewhere on the board
PCIE30X2_PERSTn_M2: R153.1; also elsewhere on the board
PCIE30X2_WAKEn_M2: R154.1; also elsewhere on the board
PCIE30_REFCLKN_CON: CN2.53, R157.1, R159.1
PCIE30_REFCLKN_IN: R162.1, R163.1, U1.AA25 (PCIE30_REFCLKN_IN)
PCIE30_REFCLKP_CON: CN2.55, R158.1, R160.1
PCIE30_REFCLKP_IN: R161.1, R164.1, U1.Y25 (PCIE30_REFCLKP_IN)
PCIE30_RX0N: CN2.41, U1.AC27 (PCIE30_RX0N)
PCIE30_RX0P: CN2.43, U1.AC28 (PCIE30_RX0P)
PCIE30_RX1N: CN2.29, U1.AD27 (PCIE30_RX1N)
PCIE30_RX1P: CN2.31, U1.AD28 (PCIE30_RX1P)
PCIE30_TX0N: C298.2, U1.AA27 (PCIE30_TX0N)
PCIE30_TX0P: C297.2, U1.AA28 (PCIE30_TX0P)
PCIE30_TX1N: C299.2, U1.AB27 (PCIE30_TX1N)
PCIE30_TX1P: C300.2, U1.AB28 (PCIE30_TX1P)
PCIE_PWREN_H_GPIO0_D4: R173.2, R174.1; also elsewhere on the board
VCC3V3_PCIE30: C301.1, C302.1, C303.1, C304.1, C318.1, C319.1, C320.1, C321.1, CN2.2, CN2.4, CN2.70, CN2.72, CN2.74, L11.2, R175.1
VCC3V3_PI6C_03: C307.1, C308.1, C311.1, C314.1, R156.1, R166.2, R168.2, R170.2, R172.2, U46.16 (VDDX), U50.5 (OUT)
VCCA_1V8: C349.1, C350.1, U1.U22 (PCIE30_AVDD_1V8); also elsewhere on the board
VCC_SYSIN: C312.1, C315.1, C316.1, U50.1 (VIN), U51.4 (IN); also elsewhere on the board
VDDA_0V9: C347.1, C348.1, U1.U20 (PCIE30_AVDD_0V9), U1.U21 (PCIE30_AVDD_0V9); also elsewhere on the board

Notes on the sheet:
Diff 100 Ohm ±10%
M.2 Type B
Diff 85 Ohm ±10%
RK3568
Clock Generator
Frost
Power / Decoupling

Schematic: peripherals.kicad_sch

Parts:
C1, C2: 10pF C0G 50V; C_0402_1005Metric
C198, C253: 100nF X5R 10V; C_0402_1005Metric
C252: 220pF C0G 25V; C_0402_1005Metric
C284, C286, C288, C289, C292, C293, C294, C295, C358, C359: 100nF X5R 10V; C_0201_0603Metric
C285, C287, C290, C291, C296: 1uF X5R 10V; C_0402_1005Metric
C353, C354, C355, C356, C357: 1nF X5R 10V; C_0402_1005Metric
CN1: PJ-393 8PJ; AUDIO-SMD_PJ-393-8PJ; LCSC Part C668609
J4: Conn_01x04; PinHeader_1x04_P2.54mm_Vertical
R1: 22R 5%; R_0402_1005Metric
R2: 1M 5%; R_0402_1005Metric
R129: 1K 5%; R_0402_1005Metric
R139, R148, R149: 100K 5%; R_0402_1005Metric
R140, R141, R145, R151: 0R 5%; R_0402_1005Metric
R146, R193, R194: 2.2K 5%; R_0402_1005Metric
R147, R180, R181, R183, R184, R185: 100R 5%; R_0402_1005Metric
R182: 120R 5%; R_0402_1005Metric
R186, R188: 10K 1%; R_0402_1005Metric
R187, R189: 10K 1%; R_0402_1005Metric; not fitted
R198, R199: 10K 5%; R_0402_1005Metric
SW1, SW2, SW3: TS24CA; SW-SMD_2P-TS24CA; LCSC Part C393942
TP10, TP11: TestPoint; TestPoint_Pad_D1.0mm
U1: RK3568; BGA636C65P28X28_1900X1900X168; PARTREV 1.3; LCSC C3345225
U47, U48, U49, U58, U59, U60, U61, U62: ESD5451N_C5261080; DFN1006-2L-BI; LCSC Part C5261080
X1: 24 MHz; CRYSTAL-SMD_4P-L3.2-W2.5-BL; LCSC C15643

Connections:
/Peripherals/XIN24M: C2.1, R2.2, U1.AF28 (XIN24M), X1.1
/Peripherals/XOUT24M: R1.1, R2.1, U1.AF27 (XOUT24M)
BATT_TC_L: C357.1, R198.1, U1.G21 (SARADC_VIN4)
BT_REG_ON_H_GPIO0_C1: U1.AF23 (GPIO0_C1_D); also elsewhere on the board
BT_WAKE_HOST_H_GPIO0_B7: U1.AH26 (GPIO0_B7_D); also elsewhere on the board
CHG_INT_L_GPIO0_C2: U1.AG23 (GPIO0_C2_D); also elsewhere on the board
DVP_PWREN0_H_GPIO0_D3: U1.AE26 (GPIO0_D3_D); also elsewhere on the board
FLASH_VOL_SEL: U1.AG25 (GPIO0_A7_U); also elsewhere on the board
HALL_INT_L_GPIO0_C6: U1.AD20 (GPIO0_C6_D); also elsewhere on the board
HOST_WAKE_BT_H_GPIO0_B0: U1.AD23 (GPIO0_B0_U); also elsewhere on the board
HPL_OUT: R140.2; also elsewhere on the board
HPR_OUT: R141.2; also elsewhere on the board
HP_DET_L_GPIO3_C2: C198.1, R129.2, R139.2; also elsewhere on the board
HP_SNS: R145.2; also elsewhere on the board
I2C0_SCL_PMIC: R193.2, U1.AF24 (GPIO0_B1_U); also elsewhere on the board
I2C0_SDA_PMIC: R194.2, U1.AB21 (GPIO0_B2_U); also elsewhere on the board
LCD0_BL_PWM4: U1.AE23 (GPIO0_C3_D); also elsewhere on the board
LCD0_PWREN_H_GPIO0_C7: U1.AH25 (GPIO0_C7_D); also elsewhere on the board
MIC1_INN: R146.2; also elsewhere on the board
unnamed: C1.1, R1.2, X1.3
unnamed: C252.1, CN1.4, CN1.8, R146.1, R147.2, R148.1, U49.2
unnamed: CN1.1, CN1.5, R140.1, U48.2
unnamed: CN1.2, CN1.6, R141.1, U47.2
unnamed: CN1.3, R129.1
unnamed: J4.2, R180.1, U59.1
unnamed: J4.3, R181.1, U58.1
unnamed: R183.1, SW1.2, U60.1
unnamed: R184.1, SW2.2, U61.1
unnamed: R185.1, SW3.2
PCIE_PWREN_H_GPIO0_D4: U1.AB23 (GPIO0_D4_D); also elsewhere on the board
PMIC_INT_L: U1.AA22 (GPIO0_A3_U); also elsewhere on the board
PMIC_PWRON: R183.2; also elsewhere on the board
PMIC_SLEEP_H: U1.AG28 (GPIO0_A2_D); also elsewhere on the board
PMUIO2: C294.1, J4.1, R193.1, R194.1, U1.W19 (PMUIO2); also elsewhere on the board
RESETn: C292.1, R151.1, R184.2, U1.AH27 (~POR_U); also elsewhere on the board
SARADC_VIN0_KEY/RECOVERY: C353.1, R185.2, R199.1, TP10.1, U1.B27 (SARADC_VIN0), U62.1
SARADC_VIN1_HW_ID: C354.1, R186.2, R187.1, U1.C26 (SARADC_VIN1)
SARADC_VIN2_HP_HOOK: C253.1, C355.1, R148.2, R149.1, U1.D24 (SARADC_VIN2)
SARADC_VIN3_BOM_ID: C356.1, R188.2, R189.1, U1.E23 (SARADC_VIN3)
SDMMC0_DET_L: U1.Y22 (GPIO0_A4_U); also elsewhere on the board
SDMMC0_PWREN_L: U1.AF25 (GPIO0_A5_D); also elsewhere on the board
TSADC_SHUT_M0: R151.2, U1.AG26 (GPIO0_A1_Z)
UART2_RX_M0_DEBUG: R180.2, R182.1, U1.AC20 (GPIO0_D0_U)
UART2_TX_M0_DEBUG: R181.2, U1.AH24 (GPIO0_D1_U)
USB5V0_EN_H_GPIO0_D6: U1.AC24 (GPIO0_D6_D); also elsewhere on the board
USBCC_INT_L_GPIO0_C5: U1.AC21 (GPIO0_C5_D); also elsewhere on the board
USB_HOST_PWREN_H_GPIO0_A6: U1.AE24 (GPIO0_A6_D); also elsewhere on the board
VCC3V3_PMU: C293.1, U1.Y20 (PMUIO1); also elsewhere on the board
VCCA1V8_PMU: C286.1, C287.1, U1.Y21 (PMUPLL_AVDD_1V8); also elsewhere on the board
VCCA_1V8: C289.1, C291.1, C359.1, R198.2, R199.2, U1.H22 (SARADC_AVDD_1V8), U1.N10 (SYSPLL_AVDD_1V8); also elsewhere on the board
VCCIO_ACODEC: R147.1; also elsewhere on the board
VCC_1V8: C358.1, R139.1, R186.1, R188.1, U1.H20 (OTP_VCC18); also elsewhere on the board
VDDA0V9_PMU: C284.1, C285.1, C295.1, C296.1, U1.V19 (PMU_VDD_LOGIC_0V9), U1.V21 (PMUPLL_AVDD_0V9); also elsewhere on the board
VDDA_0V9: C288.1, C290.1, U1.P11 (SYSPLL_AVDD_0V9); also elsewhere on the board
WIFI_PWREN_GPIO0_A0: U1.AG27 (GPIO0_A0_D)
WIFI_REG_ON_H_GPIO0_C0: U1.AD22 (GPIO0_C0_D); also elsewhere on the board
WIFI_WAKE_HOST_H_GPIO0_C4: U1.AD21 (GPIO0_C4_D); also elsewhere on the board

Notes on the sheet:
If SARADC_VIN0=0V at after power on and reset, then system will enter into loader mode.
HW / BOM ID
RK3568
Headphone Jack
Caps should be placed under RK3568
Debug UART
Recovery
Frost
Crystal
Reset
I2C1
Power On
Stuff for 1.8V, empty for 3.3V
